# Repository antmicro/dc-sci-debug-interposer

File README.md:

# DC-SCI Debug Interposer

Copyright (c) 2026 [Antmicro](https://www.antmicro.com)

## Overview

This project includes desing files for a printed circuit board that can be connected between DC-SCM (BMC) unit and host (server) platform that is controlled by the BMC.
The board exposes all relevant IO interfaces provided by the DC-SCI rev.2.x. in order to streamline the DC-SCM software development and aid the server platform (HPM) bringup.
All single-ended signals are exposed on 2.54 mm headers to simplify the debugging setup.
The on-board SOP-16 sockets provide an easy way for BIOS injection.
The DC-SCI Debug Interposer board also exposes two USB headers connected to the `PCIE_HPMROOT_5` interface compatible with HPM Common Circuit Type 1 Design Specification.

## Key features

* Compatible with DC-SCM 2.x
* All single ended DC-SCI signals exposed on 2.54 mm (0.1 inch) pin headers
* Two sockets for SPI Flash memories with BIOS image
* 2-port USB controller connected to DC-SCI PCIE_HPMROOT_5 (assembly option)
* 68 x 90 mm (2.67 x 3.54 inch) PCB outline

## Project structure

The main directory contains KiCad PCB project files, the LICENSE, and this README, and the img directory contains graphics for this README.

## License

This project is licensed under the [Apache-2.0](LICENSE) license.

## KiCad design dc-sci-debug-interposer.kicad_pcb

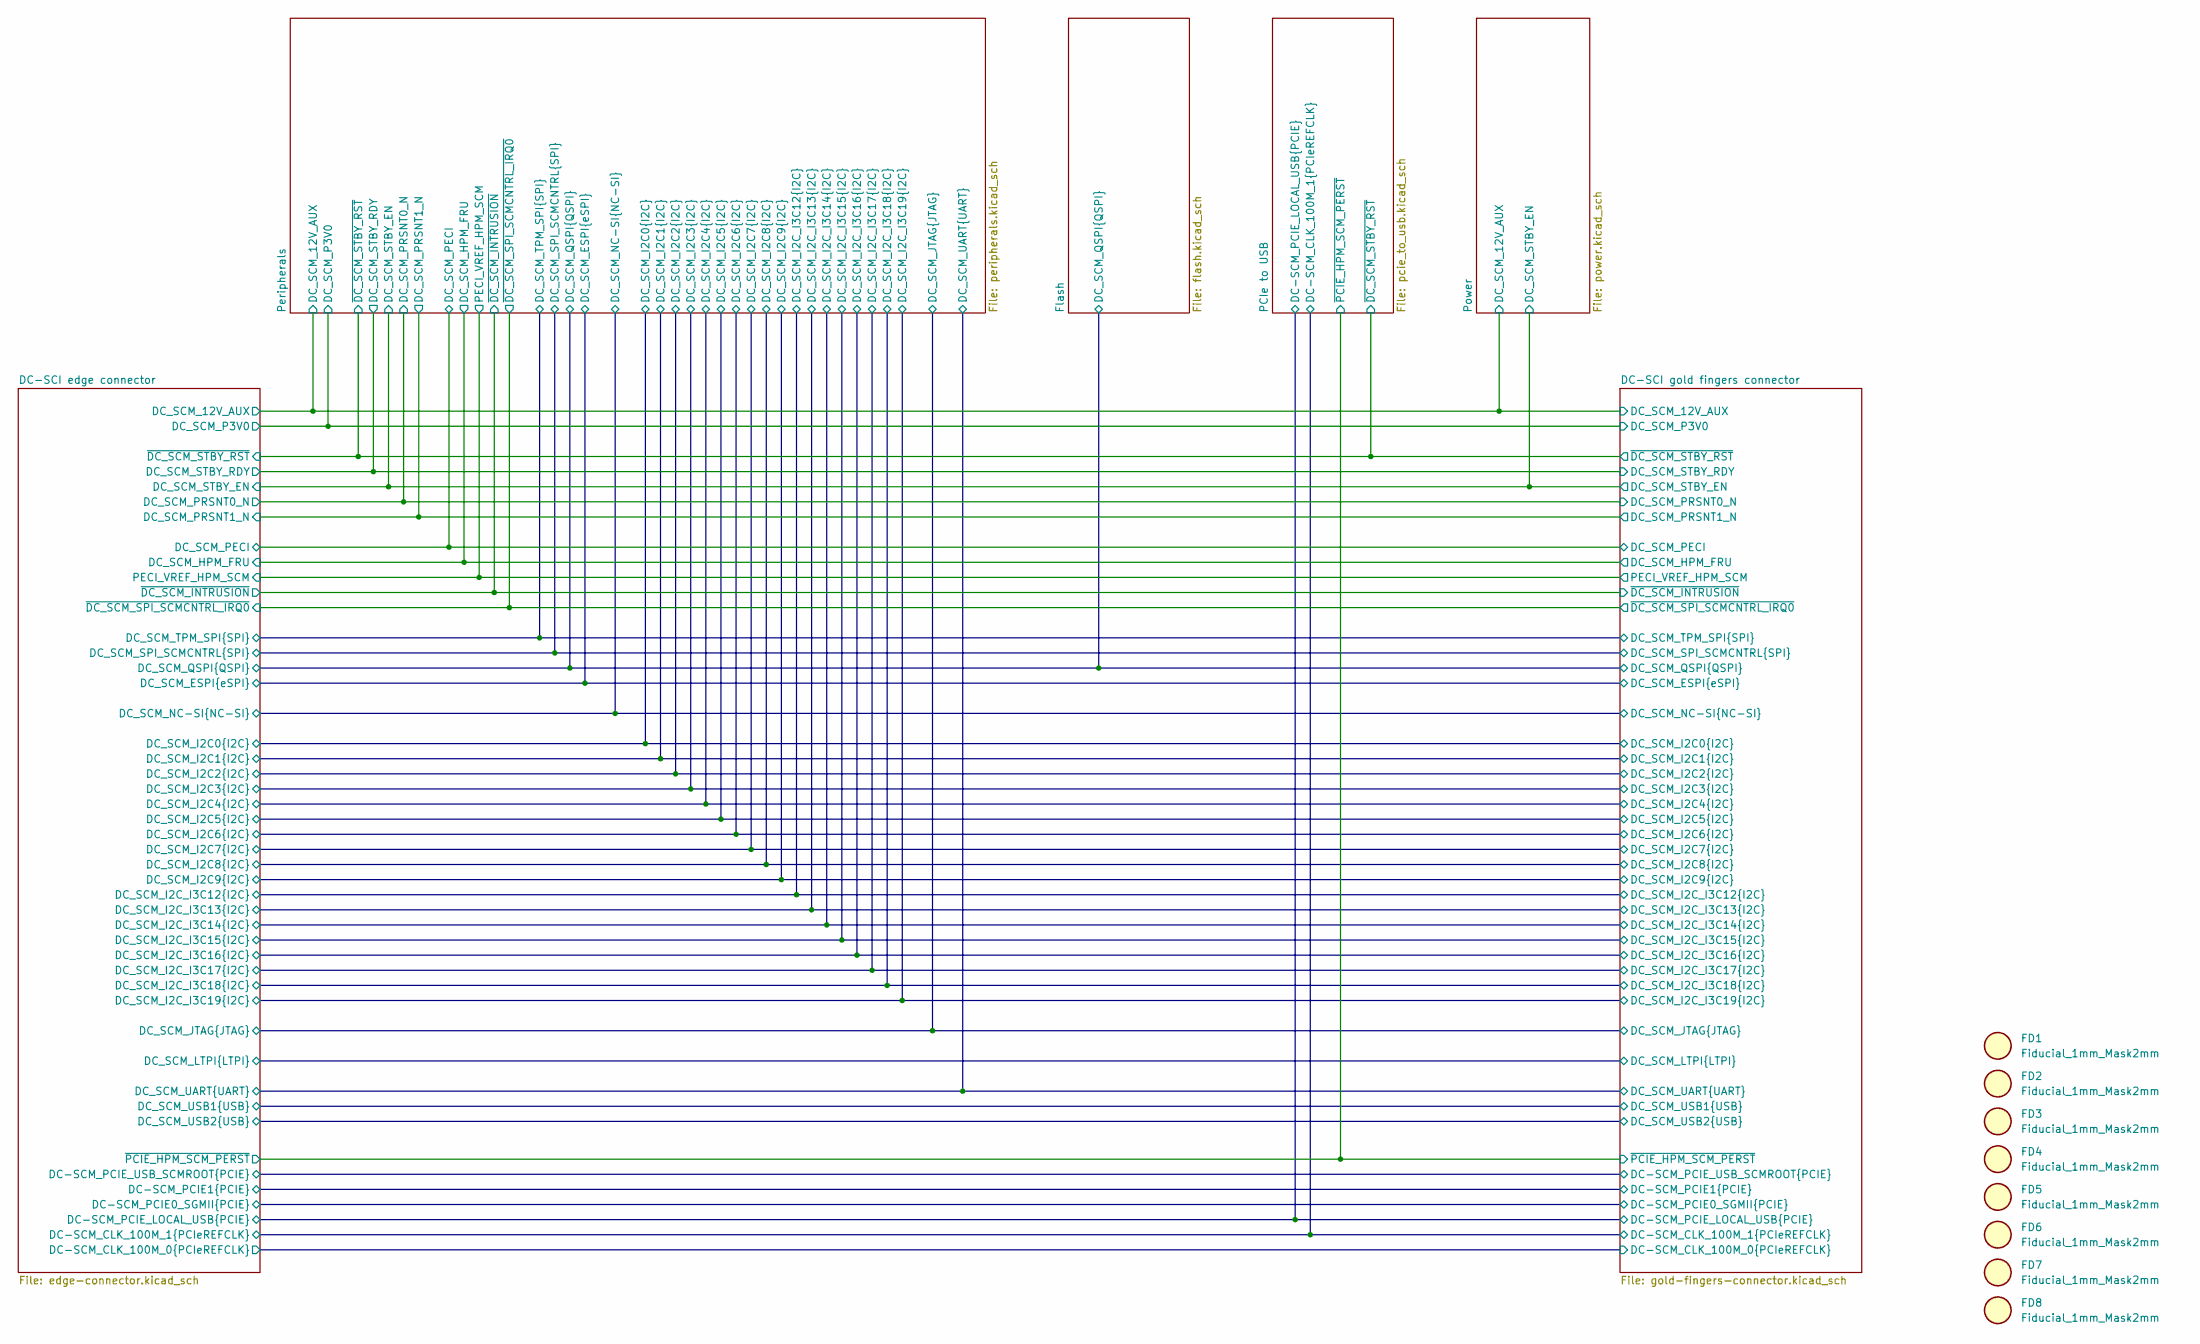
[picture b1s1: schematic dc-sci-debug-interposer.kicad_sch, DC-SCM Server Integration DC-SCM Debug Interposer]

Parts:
FD1, FD2, FD3, FD4, FD5, FD6, FD7, FD8: Fiducial_1mm_Mask2mm

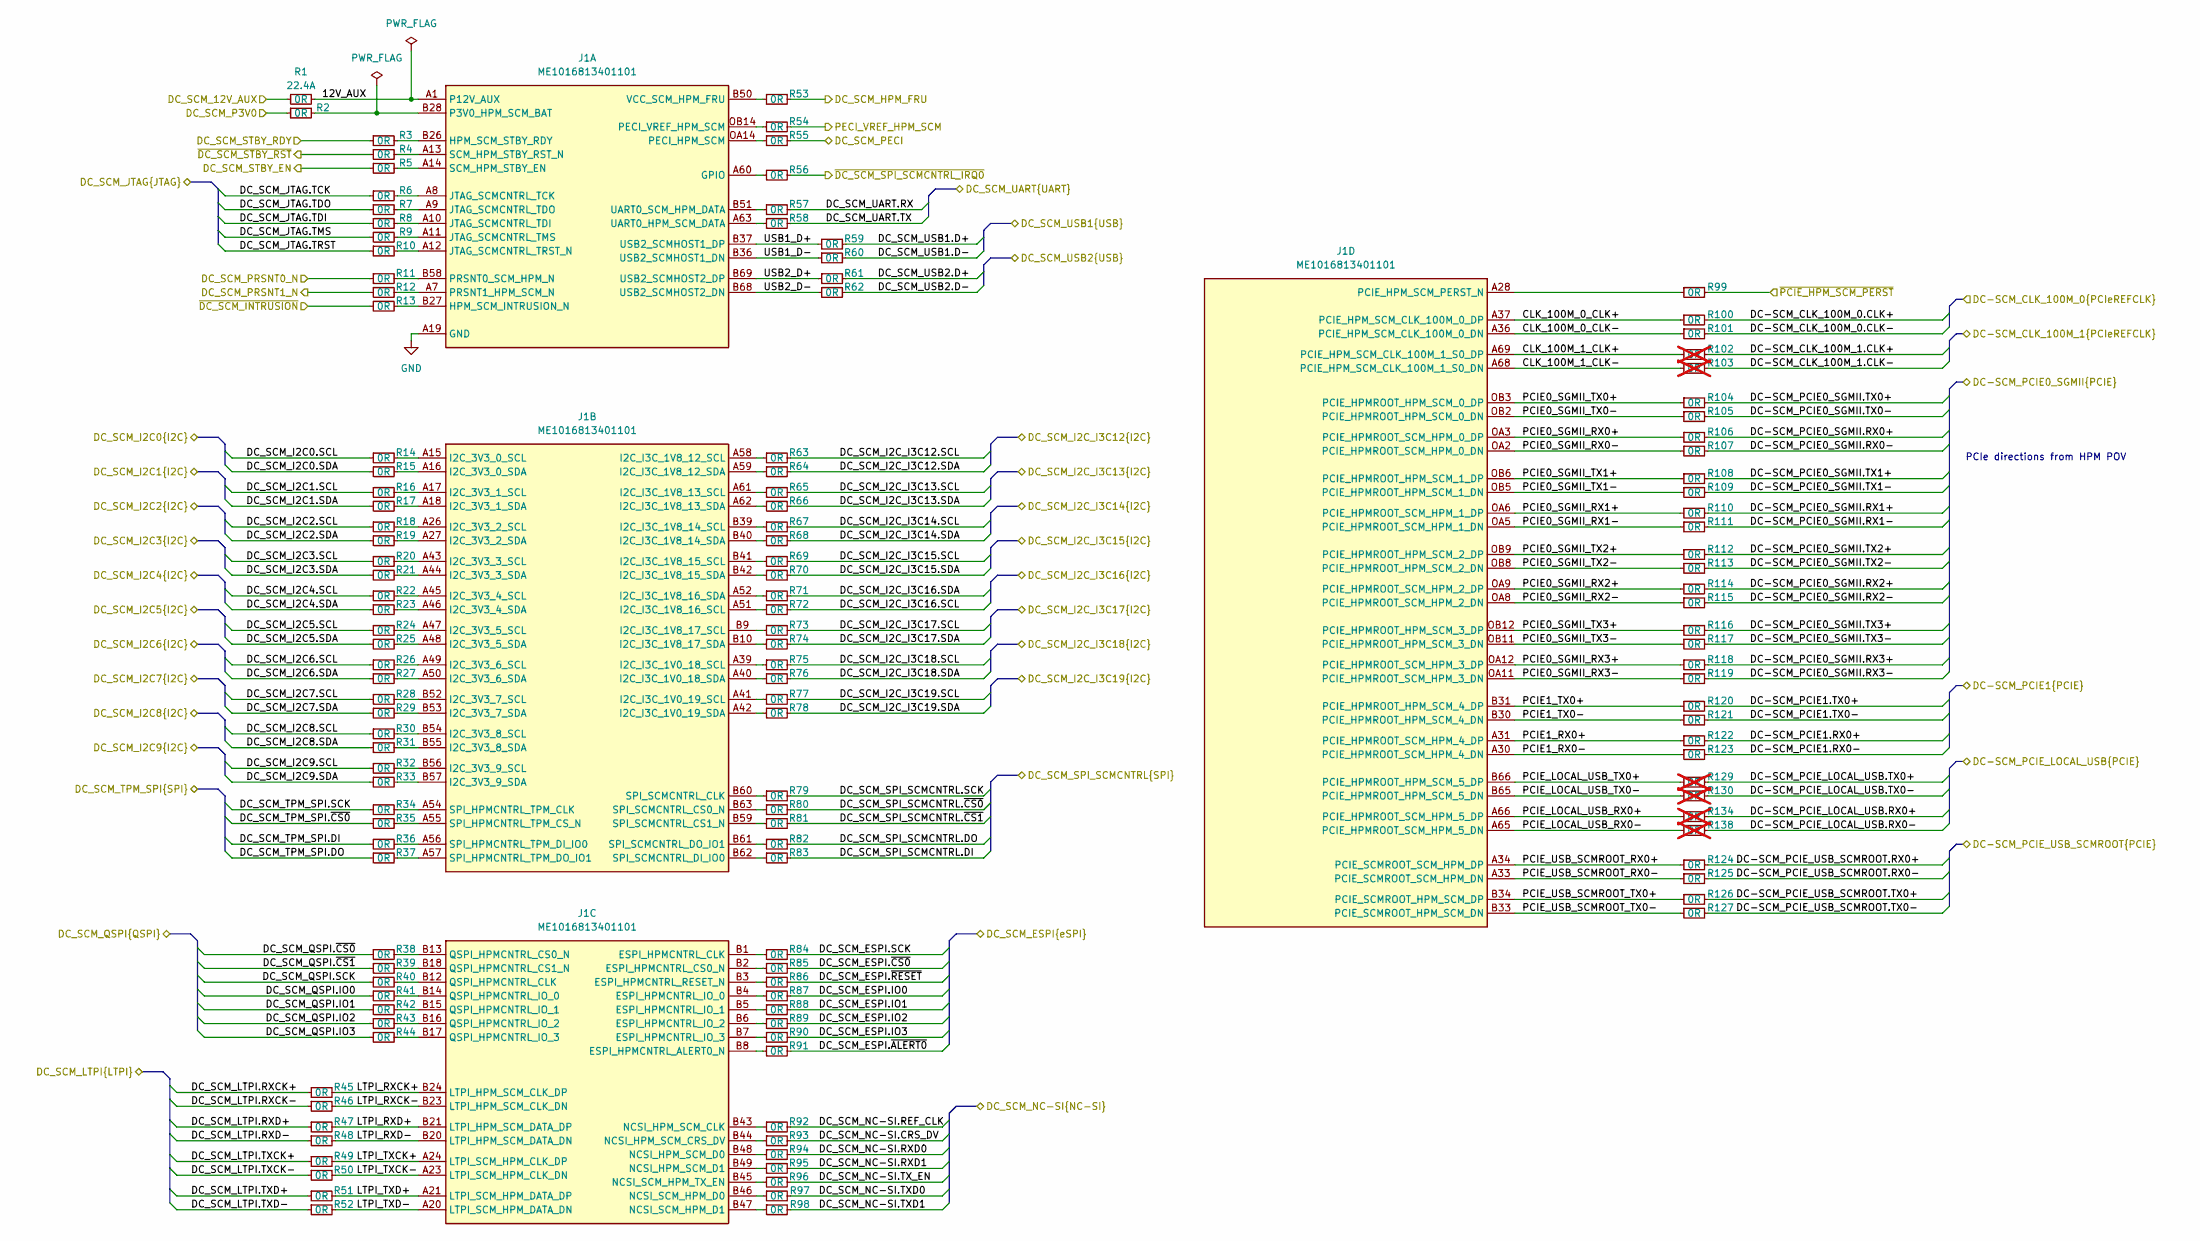
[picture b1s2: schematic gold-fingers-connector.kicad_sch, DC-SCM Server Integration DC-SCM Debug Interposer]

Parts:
J1: Socket_DC-SCM-2.1_2x84_Rev-1-1_CUSTOM; Socket_DC-SCM-2.1_2x84_Rev-1-1; MPN ME1016813401101
R1: R_0R_22.4A_0603; R_0603_1608Metric; Tolerance template_tolerance; MPN PMR03EZPJ000
R2, R3, R4, R5, R6, R7, R8, R9, R10, R11, R12, R13, R14, R15, R16, R17, R18, R19, R20, R21, R22, R23, R24, R25, R26, R27, R28, R29, R30, R31, R32, R33, R34, R35, R36, R37, R38, R39, R40, R41, R42, R43, R44, R45, R46, R47, R48, R49, R50, R51, R52, R53, R54, R55, R56, R57, R58, R59, R60, R61, R62, R63, R64, R65, R66, R67, R68, R69, R70, R71, R72, R73, R74, R75, R76, R77, R78, R79, R80, R81, R82, R83, R84, R85, R86, R87, R88, R89, R90, R91, R92, R93, R94, R95, R96, R97, R98, R99, R100, R101, R104, R105, R106, R107, R108, R109, R110, R111, R112, R113, R114, R115, R116, R117, R118, R119, R120, R121, R122, R123, R124, R125, R126, R127: R_0R_0402; R_0402_1005Metric; MPN ERJ2GE0R00X
R102, R103, R129, R130, R134, R138: R_0R_0402; R_0402_1005Metric; MPN ERJ2GE0R00X; not fitted

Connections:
/DC-SCI edge connector/DC-SCM_CLK_100M_0.CLK+: R100.2; also elsewhere on the board
/DC-SCI edge connector/DC-SCM_CLK_100M_0.CLK-: R101.2; also elsewhere on the board
/DC-SCI edge connector/DC-SCM_CLK_100M_1.CLK+: R102.2; also elsewhere on the board
/DC-SCI edge connector/DC-SCM_CLK_100M_1.CLK-: R103.2; also elsewhere on the board
/DC-SCI edge connector/DC-SCM_PCIE0_SGMII.RX0+: R106.2; also elsewhere on the board
/DC-SCI edge connector/DC-SCM_PCIE0_SGMII.RX0-: R107.2; also elsewhere on the board
/DC-SCI edge connector/DC-SCM_PCIE0_SGMII.RX1+: R110.2; also elsewhere on the board
/DC-SCI edge connector/DC-SCM_PCIE0_SGMII.RX1-: R111.2; also elsewhere on the board
/DC-SCI edge connector/DC-SCM_PCIE0_SGMII.RX2+: R114.2; also elsewhere on the board
/DC-SCI edge connector/DC-SCM_PCIE0_SGMII.RX2-: R115.2; also elsewhere on the board
/DC-SCI edge connector/DC-SCM_PCIE0_SGMII.RX3+: R118.2; also elsewhere on the board
/DC-SCI edge connector/DC-SCM_PCIE0_SGMII.RX3-: R119.2; also elsewhere on the board
/DC-SCI edge connector/DC-SCM_PCIE0_SGMII.TX0+: R104.2; also elsewhere on the board
/DC-SCI edge connector/DC-SCM_PCIE0_SGMII.TX0-: R105.2; also elsewhere on the board
/DC-SCI edge connector/DC-SCM_PCIE0_SGMII.TX1+: R108.2; also elsewhere on the board
/DC-SCI edge connector/DC-SCM_PCIE0_SGMII.TX1-: R109.2; also elsewhere on the board
/DC-SCI edge connector/DC-SCM_PCIE0_SGMII.TX2+: R112.2; also elsewhere on the board
/DC-SCI edge connector/DC-SCM_PCIE0_SGMII.TX2-: R113.2; also elsewhere on the board
/DC-SCI edge connector/DC-SCM_PCIE0_SGMII.TX3+: R116.2; also elsewhere on the board
/DC-SCI edge connector/DC-SCM_PCIE0_SGMII.TX3-: R117.2; also elsewhere on the board
/DC-SCI edge connector/DC-SCM_PCIE1.RX0+: R122.2; also elsewhere on the board
/DC-SCI edge connector/DC-SCM_PCIE1.RX0-: R123.2; also elsewhere on the board
/DC-SCI edge connector/DC-SCM_PCIE1.TX0+: R120.2; also elsewhere on the board
/DC-SCI edge connector/DC-SCM_PCIE1.TX0-: R121.2; also elsewhere on the board
/DC-SCI edge connector/DC-SCM_PCIE_LOCAL_USB.RX0+: R134.2; also elsewhere on the board
/DC-SCI edge connector/DC-SCM_PCIE_LOCAL_USB.RX0-: R138.2; also elsewhere on the board
/DC-SCI edge connector/DC-SCM_PCIE_LOCAL_USB.TX0+: R129.2; also elsewhere on the board
/DC-SCI edge connector/DC-SCM_PCIE_LOCAL_USB.TX0-: R130.2; also elsewhere on the board
/DC-SCI edge connector/DC-SCM_PCIE_USB_SCMROOT.RX0+: R124.2; also elsewhere on the board
/DC-SCI edge connector/DC-SCM_PCIE_USB_SCMROOT.RX0-: R125.2; also elsewhere on the board
/DC-SCI edge connector/DC-SCM_PCIE_USB_SCMROOT.TX0+: R126.2; also elsewhere on the board
/DC-SCI edge connector/DC-SCM_PCIE_USB_SCMROOT.TX0-: R127.2; also elsewhere on the board
/DC-SCI edge connector/DC_SCM_12V_AUX: R1.1; also elsewhere on the board
/DC-SCI edge connector/DC_SCM_ESPI.IO0: R87.2; also elsewhere on the board
/DC-SCI edge connector/DC_SCM_ESPI.IO1: R88.2; also elsewhere on the board
/DC-SCI edge connector/DC_SCM_ESPI.IO2: R89.2; also elsewhere on the board
/DC-SCI edge connector/DC_SCM_ESPI.IO3: R90.2; also elsewhere on the board
/DC-SCI edge connector/DC_SCM_ESPI.SCK: R84.2; also elsewhere on the board
/DC-SCI edge connector/DC_SCM_ESPI.~ALERT0: R91.2; also elsewhere on the board
/DC-SCI edge connector/DC_SCM_ESPI.~CS0: R85.2; also elsewhere on the board
/DC-SCI edge connector/DC_SCM_ESPI.~RESET: R86.2; also elsewhere on the board
/DC-SCI edge connector/DC_SCM_HPM_FRU: R53.2; also elsewhere on the board
/DC-SCI edge connector/DC_SCM_I2C0.SCL: R14.1; also elsewhere on the board
/DC-SCI edge connector/DC_SCM_I2C0.SDA: R15.1; also elsewhere on the board
/DC-SCI edge connector/DC_SCM_I2C1.SCL: R16.1; also elsewhere on the board
/DC-SCI edge connector/DC_SCM_I2C1.SDA: R17.1; also elsewhere on the board
/DC-SCI edge connector/DC_SCM_I2C2.SCL: R18.1; also elsewhere on the board
/DC-SCI edge connector/DC_SCM_I2C2.SDA: R19.1; also elsewhere on the board
/DC-SCI edge connector/DC_SCM_I2C3.SCL: R20.1; also elsewhere on the board
/DC-SCI edge connector/DC_SCM_I2C3.SDA: R21.1; also elsewhere on the board
/DC-SCI edge connector/DC_SCM_I2C4.SCL: R22.1; also elsewhere on the board
/DC-SCI edge connector/DC_SCM_I2C4.SDA: R23.1; also elsewhere on the board
/DC-SCI edge connector/DC_SCM_I2C5.SCL: R24.1; also elsewhere on the board
/DC-SCI edge connector/DC_SCM_I2C5.SDA: R25.1; also elsewhere on the board
/DC-SCI edge connector/DC_SCM_I2C6.SCL: R26.1; also elsewhere on the board
/DC-SCI edge connector/DC_SCM_I2C6.SDA: R27.1; also elsewhere on the board
/DC-SCI edge connector/DC_SCM_I2C7.SCL: R28.1; also elsewhere on the board
/DC-SCI edge connector/DC_SCM_I2C7.SDA: R29.1; also elsewhere on the board
/DC-SCI edge connector/DC_SCM_I2C8.SCL: R30.1; also elsewhere on the board
/DC-SCI edge connector/DC_SCM_I2C8.SDA: R31.1; also elsewhere on the board
/DC-SCI edge connector/DC_SCM_I2C9.SCL: R32.1; also elsewhere on the board
/DC-SCI edge connector/DC_SCM_I2C9.SDA: R33.1; also elsewhere on the board
/DC-SCI edge connector/DC_SCM_I2C_I3C12.SCL: R63.2; also elsewhere on the board
/DC-SCI edge connector/DC_SCM_I2C_I3C12.SDA: R64.2; also elsewhere on the board
/DC-SCI edge connector/DC_SCM_I2C_I3C13.SCL: R65.2; also elsewhere on the board
/DC-SCI edge connector/DC_SCM_I2C_I3C13.SDA: R66.2; also elsewhere on the board
/DC-SCI edge connector/DC_SCM_I2C_I3C14.SCL: R67.2; also elsewhere on the board
/DC-SCI edge connector/DC_SCM_I2C_I3C14.SDA: R68.2; also elsewhere on the board
/DC-SCI edge connector/DC_SCM_I2C_I3C15.SCL: R69.2; also elsewhere on the board
/DC-SCI edge connector/DC_SCM_I2C_I3C15.SDA: R70.2; also elsewhere on the board
/DC-SCI edge connector/DC_SCM_I2C_I3C16.SCL: R72.2; also elsewhere on the board
/DC-SCI edge connector/DC_SCM_I2C_I3C16.SDA: R71.2; also elsewhere on the board
/DC-SCI edge connector/DC_SCM_I2C_I3C17.SCL: R73.2; also elsewhere on the board
/DC-SCI edge connector/DC_SCM_I2C_I3C17.SDA: R74.2; also elsewhere on the board
/DC-SCI edge connector/DC_SCM_I2C_I3C18.SCL: R75.2; also elsewhere on the board
/DC-SCI edge connector/DC_SCM_I2C_I3C18.SDA: R76.2; also elsewhere on the board
/DC-SCI edge connector/DC_SCM_I2C_I3C19.SCL: R77.2; also elsewhere on the board
/DC-SCI edge connector/DC_SCM_I2C_I3C19.SDA: R78.2; also elsewhere on the board
/DC-SCI edge connector/DC_SCM_JTAG.TCK: R6.1; also elsewhere on the board
/DC-SCI edge connector/DC_SCM_JTAG.TDI: R8.1; also elsewhere on the board
/DC-SCI edge connector/DC_SCM_JTAG.TDO: R7.1; also elsewhere on the board
/DC-SCI edge connector/DC_SCM_JTAG.TMS: R9.1; also elsewhere on the board
/DC-SCI edge connector/DC_SCM_JTAG.TRST: R10.1; also elsewhere on the board
/DC-SCI edge connector/DC_SCM_LTPI.RXCK+: R45.1; also elsewhere on the board
/DC-SCI edge connector/DC_SCM_LTPI.RXCK-: R46.1; also elsewhere on the board
/DC-SCI edge connector/DC_SCM_LTPI.RXD+: R47.1; also elsewhere on the board
/DC-SCI edge connector/DC_SCM_LTPI.RXD-: R48.1; also elsewhere on the board
/DC-SCI edge connector/DC_SCM_LTPI.TXCK+: R49.1; also elsewhere on the board
/DC-SCI edge connector/DC_SCM_LTPI.TXCK-: R50.1; also elsewhere on the board
/DC-SCI edge connector/DC_SCM_LTPI.TXD+: R51.1; also elsewhere on the board
/DC-SCI edge connector/DC_SCM_LTPI.TXD-: R52.1; also elsewhere on the board
/DC-SCI edge connector/DC_SCM_NC-SI.CRS_DV: R93.2; also elsewhere on the board
/DC-SCI edge connector/DC_SCM_NC-SI.REF_CLK: R92.2; also elsewhere on the board
/DC-SCI edge connector/DC_SCM_NC-SI.RXD0: R94.2; also elsewhere on the board
/DC-SCI edge connector/DC_SCM_NC-SI.RXD1: R95.2; also elsewhere on the board
/DC-SCI edge connector/DC_SCM_NC-SI.TXD0: R97.2; also elsewhere on the board
/DC-SCI edge connector/DC_SCM_NC-SI.TXD1: R98.2; also elsewhere on the board
/DC-SCI edge connector/DC_SCM_NC-SI.TX_EN: R96.2; also elsewhere on the board
/DC-SCI edge connector/DC_SCM_P3V0: R2.1; also elsewhere on the board
/DC-SCI edge connector/DC_SCM_PECI: R55.2; also elsewhere on the board
/DC-SCI edge connector/DC_SCM_PRSNT0_N: R11.1; also elsewhere on the board
/DC-SCI edge connector/DC_SCM_PRSNT1_N: R12.1; also elsewhere on the board
/DC-SCI edge connector/DC_SCM_QSPI.IO0: R41.1; also elsewhere on the board
/DC-SCI edge connector/DC_SCM_QSPI.IO1: R42.1; also elsewhere on the board
/DC-SCI edge connector/DC_SCM_QSPI.IO2: R43.1; also elsewhere on the board
/DC-SCI edge connector/DC_SCM_QSPI.IO3: R44.1; also elsewhere on the board
/DC-SCI edge connector/DC_SCM_QSPI.SCK: R40.1; also elsewhere on the board
/DC-SCI edge connector/DC_SCM_QSPI.~CS0: R38.1; also elsewhere on the board
/DC-SCI edge connector/DC_SCM_QSPI.~CS1: R39.1; also elsewhere on the board
/DC-SCI edge connector/DC_SCM_SPI_SCMCNTRL.DI: R83.2; also elsewhere on the board
/DC-SCI edge connector/DC_SCM_SPI_SCMCNTRL.DO: R82.2; also elsewhere on the board
/DC-SCI edge connector/DC_SCM_SPI_SCMCNTRL.SCK: R79.2; also elsewhere on the board
/DC-SCI edge connector/DC_SCM_SPI_SCMCNTRL.~CS0: R80.2; also elsewhere on the board
/DC-SCI edge connector/DC_SCM_SPI_SCMCNTRL.~CS1: R81.2; also elsewhere on the board
/DC-SCI edge connector/DC_SCM_STBY_EN: R5.1; also elsewhere on the board
/DC-SCI edge connector/DC_SCM_STBY_RDY: R3.1; also elsewhere on the board
/DC-SCI edge connector/DC_SCM_TPM_SPI.DI: R36.1; also elsewhere on the board
/DC-SCI edge connector/DC_SCM_TPM_SPI.DO: R37.1; also elsewhere on the board
/DC-SCI edge connector/DC_SCM_TPM_SPI.SCK: R34.1; also elsewhere on the board
/DC-SCI edge connector/DC_SCM_TPM_SPI.~CS0: R35.1; also elsewhere on the board
/DC-SCI edge connector/DC_SCM_UART.RX: R57.2; also elsewhere on the board
/DC-SCI edge connector/DC_SCM_UART.TX: R58.2; also elsewhere on the board
/DC-SCI edge connector/DC_SCM_USB1.D+: R59.2; also elsewhere on the board
/DC-SCI edge connector/DC_SCM_USB1.D-: R60.2; also elsewhere on the board
/DC-SCI edge connector/DC_SCM_USB2.D+: R61.2; also elsewhere on the board
/DC-SCI edge connector/DC_SCM_USB2.D-: R62.2; also elsewhere on the board
/DC-SCI edge connector/PECI_VREF_HPM_SCM: R54.2; also elsewhere on the board
/DC-SCI edge connector/~DC_SCM_INTRUSION: R13.1; also elsewhere on the board
/DC-SCI edge connector/~DC_SCM_SPI_SCMCNTRL_IRQ0: R56.2; also elsewhere on the board
/DC-SCI edge connector/~DC_SCM_STBY_RST: R4.1; also elsewhere on the board
/DC-SCI edge connector/~PCIE_HPM_SCM_PERST: R99.2; also elsewhere on the board
/DC-SCI gold fingers connector/12V_AUX: J1.A1 (P12V_AUX), J1.A2 (P12V_AUX), J1.A3 (P12V_AUX), J1.A4 (P12V_AUX), R1.2
/DC-SCI gold fingers connector/CLK_100M_0_CLK+: J1.A37 (PCIE_HPM_SCM_CLK_100M_0_DP), R100.1
/DC-SCI gold fingers connector/CLK_100M_0_CLK-: J1.A36 (PCIE_HPM_SCM_CLK_100M_0_DN), R101.1
/DC-SCI gold fingers connector/CLK_100M_1_CLK+: J1.A69 (PCIE_HPM_SCM_CLK_100M_1_S0_DP), R102.1
/DC-SCI gold fingers connector/CLK_100M_1_CLK-: J1.A68 (PCIE_HPM_SCM_CLK_100M_1_S0_DN), R103.1
/DC-SCI gold fingers connector/LTPI_RXCK+: J1.B24 (LTPI_HPM_SCM_CLK_DP), R45.2
/DC-SCI gold fingers connector/LTPI_RXCK-: J1.B23 (LTPI_HPM_SCM_CLK_DN), R46.2
/DC-SCI gold fingers connector/LTPI_RXD+: J1.B21 (LTPI_HPM_SCM_DATA_DP), R47.2
/DC-SCI gold fingers connector/LTPI_RXD-: J1.B20 (LTPI_HPM_SCM_DATA_DN), R48.2
/DC-SCI gold fingers connector/LTPI_TXCK+: J1.A24 (LTPI_SCM_HPM_CLK_DP), R49.2
/DC-SCI gold fingers connector/LTPI_TXCK-: J1.A23 (LTPI_SCM_HPM_CLK_DN), R50.2
/DC-SCI gold fingers connector/LTPI_TXD+: J1.A21 (LTPI_SCM_HPM_DATA_DP), R51.2
/DC-SCI gold fingers connector/LTPI_TXD-: J1.A20 (LTPI_SCM_HPM_DATA_DN), R52.2
/DC-SCI gold fingers connector/PCIE0_SGMII_RX0+: J1.OA3 (PCIE_HPMROOT_SCM_HPM_0_DP), R106.1
/DC-SCI gold fingers connector/PCIE0_SGMII_RX0-: J1.OA2 (PCIE_HPMROOT_SCM_HPM_0_DN), R107.1
/DC-SCI gold fingers connector/PCIE0_SGMII_RX1+: J1.OA6 (PCIE_HPMROOT_SCM_HPM_1_DP), R110.1
/DC-SCI gold fingers connector/PCIE0_SGMII_RX1-: J1.OA5 (PCIE_HPMROOT_SCM_HPM_1_DN), R111.1
/DC-SCI gold fingers connector/PCIE0_SGMII_RX2+: J1.OA9 (PCIE_HPMROOT_SCM_HPM_2_DP), R114.1
/DC-SCI gold fingers connector/PCIE0_SGMII_RX2-: J1.OA8 (PCIE_HPMROOT_SCM_HPM_2_DN), R115.1
/DC-SCI gold fingers connector/PCIE0_SGMII_RX3+: J1.OA12 (PCIE_HPMROOT_SCM_HPM_3_DP), R118.1
/DC-SCI gold fingers connector/PCIE0_SGMII_RX3-: J1.OA11 (PCIE_HPMROOT_SCM_HPM_3_DN), R119.1
/DC-SCI gold fingers connector/PCIE0_SGMII_TX0+: J1.OB3 (PCIE_HPMROOT_HPM_SCM_0_DP), R104.1
/DC-SCI gold fingers connector/PCIE0_SGMII_TX0-: J1.OB2 (PCIE_HPMROOT_HPM_SCM_0_DN), R105.1
/DC-SCI gold fingers connector/PCIE0_SGMII_TX1+: J1.OB6 (PCIE_HPMROOT_HPM_SCM_1_DP), R108.1
/DC-SCI gold fingers connector/PCIE0_SGMII_TX1-: J1.OB5 (PCIE_HPMROOT_HPM_SCM_1_DN), R109.1
/DC-SCI gold fingers connector/PCIE0_SGMII_TX2+: J1.OB9 (PCIE_HPMROOT_HPM_SCM_2_DP), R112.1
/DC-SCI gold fingers connector/PCIE0_SGMII_TX2-: J1.OB8 (PCIE_HPMROOT_HPM_SCM_2_DN), R113.1
/DC-SCI gold fingers connector/PCIE0_SGMII_TX3+: J1.OB12 (PCIE_HPMROOT_HPM_SCM_3_DP), R116.1
/DC-SCI gold fingers connector/PCIE0_SGMII_TX3-: J1.OB11 (PCIE_HPMROOT_HPM_SCM_3_DN), R117.1
/DC-SCI gold fingers connector/PCIE1_RX0+: J1.A31 (PCIE_HPMROOT_SCM_HPM_4_DP), R122.1
/DC-SCI gold fingers connector/PCIE1_RX0-: J1.A30 (PCIE_HPMROOT_SCM_HPM_4_DN), R123.1
/DC-SCI gold fingers connector/PCIE1_TX0+: J1.B31 (PCIE_HPMROOT_HPM_SCM_4_DP), R120.1
/DC-SCI gold fingers connector/PCIE1_TX0-: J1.B30 (PCIE_HPMROOT_HPM_SCM_4_DN), R121.1
/DC-SCI gold fingers connector/PCIE_LOCAL_USB_RX0+: J1.A66 (PCIE_HPMROOT_SCM_HPM_5_DP), R134.1
/DC-SCI gold fingers connector/PCIE_LOCAL_USB_RX0-: J1.A65 (PCIE_HPMROOT_SCM_HPM_5_DN), R138.1
/DC-SCI gold fingers connector/PCIE_LOCAL_USB_TX0+: J1.B66 (PCIE_HPMROOT_HPM_SCM_5_DP), R129.1
/DC-SCI gold fingers connector/PCIE_LOCAL_USB_TX0-: J1.B65 (PCIE_HPMROOT_HPM_SCM_5_DN), R130.1
/DC-SCI gold fingers connector/PCIE_USB_SCMROOT_RX0+: J1.A34 (PCIE_SCMROOT_SCM_HPM_DP), R124.1
/DC-SCI gold fingers connector/PCIE_USB_SCMROOT_RX0-: J1.A33 (PCIE_SCMROOT_SCM_HPM_DN), R125.1
/DC-SCI gold fingers connector/PCIE_USB_SCMROOT_TX0+: J1.B34 (PCIE_SCMROOT_HPM_SCM_DP), R126.1
/DC-SCI gold fingers connector/PCIE_USB_SCMROOT_TX0-: J1.B33 (PCIE_SCMROOT_HPM_SCM_DN), R127.1
/DC-SCI gold fingers connector/USB1_D+: J1.B37 (USB2_SCMHOST1_DP), R59.1
/DC-SCI gold fingers connector/USB1_D-: J1.B36 (USB2_SCMHOST1_DN), R60.1
/DC-SCI gold fingers connector/USB2_D+: J1.B69 (USB2_SCMHOST2_DP), R61.1
/DC-SCI gold fingers connector/USB2_D-: J1.B68 (USB2_SCMHOST2_DN), R62.1
GND: J1.A5 (GND), J1.A6 (GND), J1.A19 (GND), J1.A22 (GND), J1.A25 (GND), J1.A29 (GND), J1.A32 (GND), J1.A35 (GND), J1.A38 (GND), J1.A53 (GND), J1.A64 (GND), J1.A67 (GND), J1.A70 (GND), J1.B11 (GND), J1.B19 (GND), J1.B22 (GND), J1.B25 (GND), J1.B29 (GND), J1.B32 (GND), J1.B35 (GND), J1.B38 (GND), J1.B64 (GND), J1.B67 (GND), J1.B70 (GND), J1.OA1 (GND), J1.OA4 (GND), J1.OA7 (GND), J1.OA10 (GND), J1.OA13 (GND), J1.OB1 (GND), J1.OB4 (GND), J1.OB7 (GND), J1.OB10 (GND), J1.OB13 (GND); also elsewhere on the board
unnamed: J1.A60 (GPIO), R56.1
unnamed: J1.B27 (HPM_SCM_INTRUSION_N), R13.2
unnamed: J1.B26 (HPM_SCM_STBY_RDY), R3.2
unnamed: J1.A8 (JTAG_SCMCNTRL_TCK), R6.2
unnamed: J1.A10 (JTAG_SCMCNTRL_TDI), R8.2
unnamed: J1.A9 (JTAG_SCMCNTRL_TDO), R7.2
unnamed: J1.A11 (JTAG_SCMCNTRL_TMS), R9.2
unnamed: J1.A12 (JTAG_SCMCNTRL_TRST_N), R10.2
unnamed: J1.B28 (P3V0_HPM_SCM_BAT), R2.2
unnamed: J1.OA14 (PECI_HPM_SCM), R55.1
unnamed: J1.OB14 (PECI_VREF_HPM_SCM), R54.1
unnamed: J1.B58 (PRSNT0_SCM_HPM_N), R11.2
unnamed: J1.A7 (PRSNT1_HPM_SCM_N), R12.2
unnamed: J1.A14 (SCM_HPM_STBY_EN), R5.2
unnamed: J1.A13 (SCM_HPM_STBY_RST_N), R4.2
unnamed: J1.A63 (UART0_HPM_SCM_DATA), R58.1
unnamed: J1.B51 (UART0_SCM_HPM_DATA), R57.1
unnamed: J1.B50 (VCC_SCM_HPM_FRU), R53.1
unnamed: J1.A15 (I2C_3V3_0_SCL), R14.2
unnamed: J1.A16 (I2C_3V3_0_SDA), R15.2
unnamed: J1.A17 (I2C_3V3_1_SCL), R16.2
unnamed: J1.A18 (I2C_3V3_1_SDA), R17.2
unnamed: J1.A26 (I2C_3V3_2_SCL), R18.2
unnamed: J1.A27 (I2C_3V3_2_SDA), R19.2
unnamed: J1.A43 (I2C_3V3_3_SCL), R20.2
unnamed: J1.A44 (I2C_3V3_3_SDA), R21.2
unnamed: J1.A45 (I2C_3V3_4_SCL), R22.2
unnamed: J1.A46 (I2C_3V3_4_SDA), R23.2
unnamed: J1.A47 (I2C_3V3_5_SCL), R24.2
unnamed: J1.A48 (I2C_3V3_5_SDA), R25.2
unnamed: J1.A49 (I2C_3V3_6_SCL), R26.2
unnamed: J1.A50 (I2C_3V3_6_SDA), R27.2
unnamed: J1.B52 (I2C_3V3_7_SCL), R28.2
unnamed: J1.B53 (I2C_3V3_7_SDA), R29.2
unnamed: J1.B54 (I2C_3V3_8_SCL), R30.2
unnamed: J1.B55 (I2C_3V3_8_SDA), R31.2
unnamed: J1.B56 (I2C_3V3_9_SCL), R32.2
unnamed: J1.B57 (I2C_3V3_9_SDA), R33.2
unnamed: J1.A39 (I2C_I3C_1V0_18_SCL), R75.1
unnamed: J1.A40 (I2C_I3C_1V0_18_SDA), R76.1
unnamed: J1.A41 (I2C_I3C_1V0_19_SCL), R77.1
unnamed: J1.A42 (I2C_I3C_1V0_19_SDA), R78.1
unnamed: J1.A58 (I2C_I3C_1V8_12_SCL), R63.1
unnamed: J1.A59 (I2C_I3C_1V8_12_SDA), R64.1
unnamed: J1.A61 (I2C_I3C_1V8_13_SCL), R65.1
unnamed: J1.A62 (I2C_I3C_1V8_13_SDA), R66.1
unnamed: J1.B39 (I2C_I3C_1V8_14_SCL), R67.1
unnamed: J1.B40 (I2C_I3C_1V8_14_SDA), R68.1
unnamed: J1.B41 (I2C_I3C_1V8_15_SCL), R69.1
unnamed: J1.B42 (I2C_I3C_1V8_15_SDA), R70.1
unnamed: J1.A51 (I2C_I3C_1V8_16_SCL), R72.1
unnamed: J1.A52 (I2C_I3C_1V8_16_SDA), R71.1
unnamed: J1.B9 (I2C_I3C_1V8_17_SCL), R73.1
unnamed: J1.B10 (I2C_I3C_1V8_17_SDA), R74.1
unnamed: J1.A54 (SPI_HPMCNTRL_TPM_CLK), R34.2
unnamed: J1.A55 (SPI_HPMCNTRL_TPM_CS_N), R35.2
unnamed: J1.A56 (SPI_HPMCNTRL_TPM_DI_IO0), R36.2
unnamed: J1.A57 (SPI_HPMCNTRL_TPM_DO_IO1), R37.2
unnamed: J1.B60 (SPI_SCMCNTRL_CLK), R79.1
unnamed: J1.B63 (SPI_SCMCNTRL_CS0_N), R80.1
unnamed: J1.B59 (SPI_SCMCNTRL_CS1_N), R81.1
unnamed: J1.B62 (SPI_SCMCNTRL_DI_IO0), R83.1
unnamed: J1.B61 (SPI_SCMCNTRL_DO_IO1), R82.1
unnamed: J1.B8 (ESPI_HPMCNTRL_ALERT0_N), R91.1
unnamed: J1.B1 (ESPI_HPMCNTRL_CLK), R84.1
unnamed: J1.B2 (ESPI_HPMCNTRL_CS0_N), R85.1
unnamed: J1.B4 (ESPI_HPMCNTRL_IO_0), R87.1
unnamed: J1.B5 (ESPI_HPMCNTRL_IO_1), R88.1
unnamed: J1.B6 (ESPI_HPMCNTRL_IO_2), R89.1
unnamed: J1.B7 (ESPI_HPMCNTRL_IO_3), R90.1
unnamed: J1.B3 (ESPI_HPMCNTRL_RESET_N), R86.1
unnamed: J1.B43 (NCSI_HPM_SCM_CLK), R92.1
unnamed: J1.B44 (NCSI_HPM_SCM_CRS_DV), R93.1
unnamed: J1.B48 (NCSI_HPM_SCM_D0), R94.1
unnamed: J1.B49 (NCSI_HPM_SCM_D1), R95.1
unnamed: J1.B46 (NCSI_SCM_HPM_D0), R97.1
unnamed: J1.B47 (NCSI_SCM_HPM_D1), R98.1
unnamed: J1.B45 (NCSI_SCM_HPM_TX_EN), R96.1
unnamed: J1.B12 (QSPI_HPMCNTRL_CLK), R40.2
unnamed: J1.B13 (QSPI_HPMCNTRL_CS0_N), R38.2
unnamed: J1.B18 (QSPI_HPMCNTRL_CS1_N), R39.2
unnamed: J1.B14 (QSPI_HPMCNTRL_IO_0), R41.2
unnamed: J1.B15 (QSPI_HPMCNTRL_IO_1), R42.2
unnamed: J1.B16 (QSPI_HPMCNTRL_IO_2), R43.2
unnamed: J1.B17 (QSPI_HPMCNTRL_IO_3), R44.2
unnamed: J1.A28 (PCIE_HPM_SCM_PERST_N), R99.1

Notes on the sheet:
PCIe directions from HPM POV

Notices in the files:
parts and their libraries:
License: Apache-2.0
